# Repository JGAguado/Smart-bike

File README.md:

[![GitHub Release][releases-shield]][releases]
[![License][license-shield]](LICENSE)

[![Project Maintenance][maintenance-shield]][maintenance]
[![BuyMeCoffee][buymecoffee-shield]][buymecoffee]

# μBike
RP2040 microcontroller based board for standard bikes applications: lights control, GPS location with LoRa telemetry and display unit.

## Project tree
---

<li><a href="./uBike/Design/">Design</a></li>
<li><a href="./uBike/Documentation/">Documentation</a></li>

<li><a href="./README.md">README.md</a></li>

## Acknowledgments
---
 * [SparkFun Thing Plus RP2040](https://github.com/sparkfun/SparkFun_Thing_Plus-RP2040) - This board was used as inspiration for the layout design of the μBike

[releases-shield]: https://img.shields.io/github/release/JGAguado/uBike.svg?style=for-the-badge
[releases]: https://github.com/JGAguado/Fuel_Tracker/releases

[license-shield]: https://img.shields.io/badge/License-CC%20BY--NC--SA%204.0-lightgrey.svg?style=for-the-badge

[maintenance-shield]: https://img.shields.io/badge/maintainer-J.%20G.%20Aguado-blue.svg?style=for-the-badge
[maintenance]: https://github.com/JGAguado

[buymecoffee-shield]: https://img.shields.io/badge/buy%20me%20a%20coffee-support-yellow.svg?style=for-the-badge
[buymecoffee]: https://www.buymeacoffee.com/J.G.Aguado

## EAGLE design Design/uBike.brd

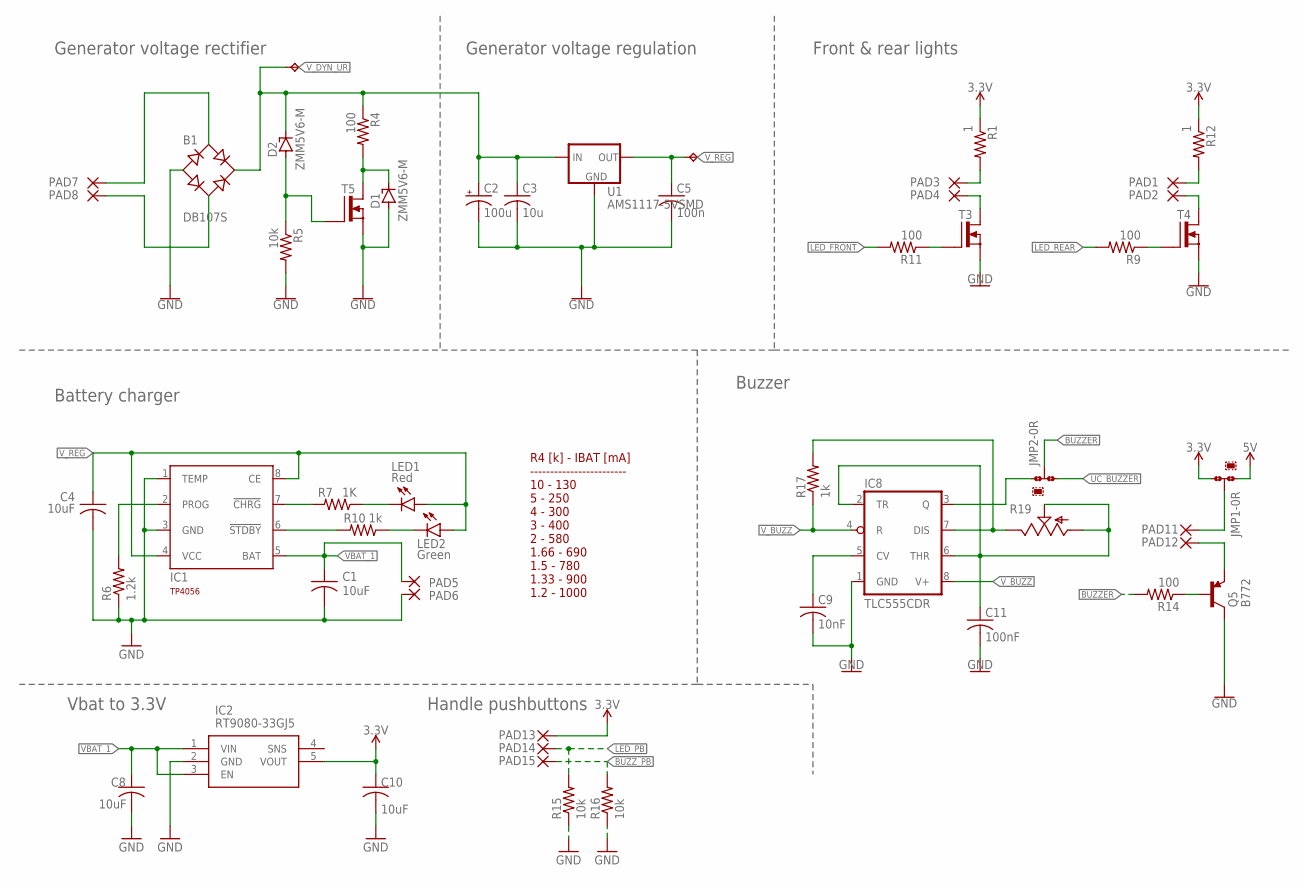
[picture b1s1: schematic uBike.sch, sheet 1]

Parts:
B1: DB107S; DBS; LCSC C5377
C1, C4, C8, C10: 10uF; C0603
C2: 100u; B/3528-21R; LCSC C16133
C3: 10u; C0603
C5: 100n; C0603
C9: 10nF; C0603
C11: 100nF; C0603
D1, D2: ZMM5V6-M; MELF-MLL34
IC1: TP4056; SOT23-8; LCSC C16581
IC2: RT9080-33GJ5; SOT94P280X100-5N; LCSC C841192
IC8: TLC555CDR; SO08; LCSC C6986
JMP1, JMP2: 0R-JUMPA; A0R-JMP
LED1: Red; LED_0603
LED2: Green; LED_0603
PAD1, PAD2, PAD3, PAD4, PAD5, PAD6, PAD7, PAD8, PAD11, PAD12, PAD13, PAD14, PAD15: SMD2; SMD1,27-2,54
Q5: B772; SOT89; LCSC C24278
R1, R12: 1; R1206; LCSC C17928
R4: 100; 0402; LCSC C17928
R5: 10k; 0402; LCSC C17928
R6: 1.2k; 0402
R7: 1K; 0402
R9, R11, R14: 100; 0402
R10, R17: 1k; 0402
R15, R16: 10k; 0402
R19: TRIM_US-RJ9W; RJ9W
T3, T4, T5: T_N-MOSFET_2N7002_CHANGJ_SOT23-GSD; SOT23
TP1, TP3: TPTP15R; TP15R
U1: AMS1117-5VSMD; SOT223

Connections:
3.3V: C10.1, IC2.5 (VOUT), JMP1.3, PAD13.1, R1.1, R12.1; also elsewhere on the board
5V: JMP1.1
BUZZER: JMP2.2, R14.2
BUZZ_PB: PAD15.1, R16.2; also elsewhere on the board
GND: B1.-, C1.2, C2.-, C3.2, C4.2, C5.2, C8.2, C9.2, C10.2, C11.2, D1.A, IC1.1 (TEMP), IC1.3 (GND), IC2.2 (GND), IC8.1 (GND), PAD6.1, Q5.2 (C), R5.2, R6.1, R15.1, R16.1, T3.2 (S), T4.2 (S), T5.2 (S), U1.1 (GND); also elsewhere on the board
LED_FRONT: R11.2; also elsewhere on the board
LED_PB: PAD14.1, R15.2; also elsewhere on the board
LED_REAR: R9.2; also elsewhere on the board
unnamed: PAD3.1, R1.2
unnamed: R9.1, T4.1 (G)
unnamed: IC1.6 (!STDBY), R10.2
unnamed: PAD4.1, T3.3 (D)
unnamed: R11.1, T3.1 (G)
unnamed: PAD2.1, T4.3 (D)
unnamed: D2.A, R5.1, T5.1 (G)
unnamed: D1.C, R4.2, T5.3 (D)
unnamed: B1.AC2, PAD8.1
unnamed: LED1.C, R7.1
unnamed: LED2.C, R10.1
unnamed: IC1.2 (PROG), R6.2
unnamed: B1.AC1, PAD7.1
unnamed: IC1.7 (!CHRG), R7.2
unnamed: Q5.1 (B), R14.1
unnamed: PAD12.1, Q5.3 (E)
unnamed: JMP1.2, PAD11.1
unnamed: PAD1.1, R12.2
unnamed: IC8.7 (DIS), R17.2, R19.E
unnamed: C11.1, IC8.2 (TR), IC8.6 (THR), R19.A, R19.S
unnamed: IC8.3 (Q), JMP2.1
unnamed: C9.1, IC8.5 (CV)
UC_BUZZER: JMP2.3; also elsewhere on the board
VBAT_1: C1.1, C8.1, IC1.5 (BAT), IC2.1 (VIN), IC2.3 (EN), PAD5.1
V_BUZZ: IC8.4 (R), IC8.8 (V+), R17.1
V_DYN_UR: B1.+, C2.+, C3.1, D2.C, R4.1, TP1.TP, U1.3 (IN)
V_REG: C4.1, C5.1, IC1.4 (VCC), IC1.8 (CE), LED1.A, LED2.A, TP3.TP, U1.2 (OUT)

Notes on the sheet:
Battery charger
R4 [k] - IBAT [mA] ------------------------ 10 - 130 5 - 250 4 - 300 3 - 400 2 - 580 1.66 - 690 1.5 - 780 1.33 - 900 1.2 - 1000
Generator voltage rectifier
Generator voltage regulation
Vbat to 3.3V
Front & rear lights
Buzzer
Handle pushbuttons

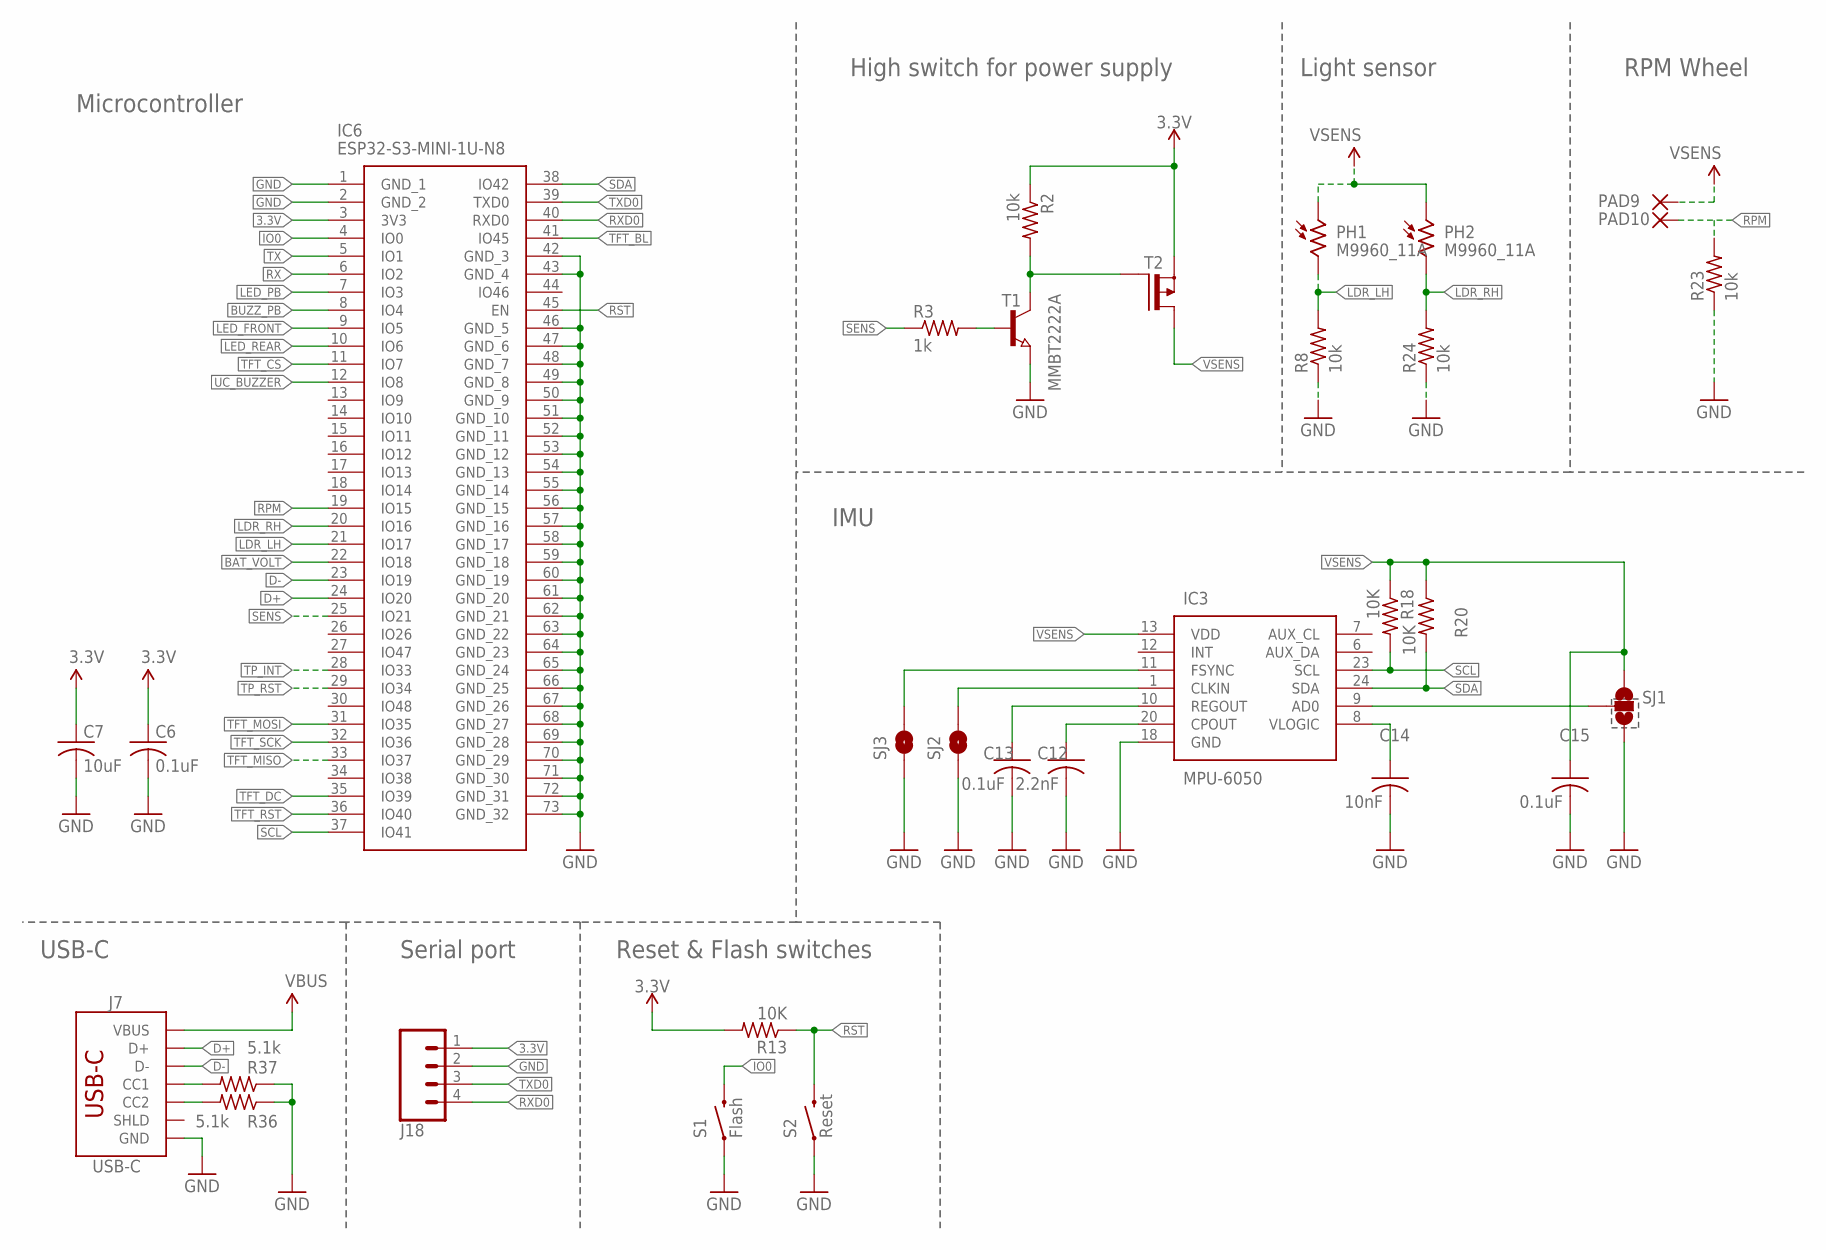
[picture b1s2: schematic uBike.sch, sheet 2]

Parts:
C6, C13, C15: 0.1uF; C0603
C7: 10uF; C0603
C12: 2.2nF; C0603
C14: 10nF; C0603
IC3: MPU-6050; MPU6050
IC6: ESP32-S3-MINI-1U-N8; ESP32S3MINI1UN8
J7: USB-C; USB-C-16P-4LAYER-ISOLATED; LCSC C2765186
J18: CONN_04PTH; 1X04
PAD9, PAD10: SMD2; SMD1,27-2,54
PH1, PH2: M9960_11A; M9960
R2, R8, R23, R24: 10k; 0402
R3: 1k; 0402
R13, R18, R20: 10K; 0402
R36, R37: 5.1k; R0603
S1: Flash; TACTILE_SWITCH_SMD_5.2MM
S2: Reset; TACTILE_SWITCH_SMD_5.2MM
SJ1: SOLDERJUMPER_2WAYPASTE2&3; SJ_3_PASTE2&3
SJ2, SJ3: SOLDERJUMPERTRACE; SJ_2S-TRACE
T1: MMBT2222A; SOT23
T2: T_P-MOSFET_SI2301CDS-T1-GE3_VISHAY_SOT23-GSD; SOT23

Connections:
3.3V: C6.1, C7.1, IC6.3 (3V3), J18.1, R2.1, R13.2, T2.2 (S); also elsewhere on the board
BAT_VOLT: IC6.22 (IO18); also elsewhere on the board
BUZZ_PB: IC6.8 (IO4); also elsewhere on the board
CC3: J7.B5 (CC2), R36.2
CC4: J7.A5 (CC1), R37.2
D+: IC6.24 (IO20), J7.A6 (D+), J7.B6 (D+)
D-: IC6.23 (IO19), J7.A7 (D-), J7.B7 (D-)
GND: C6.2, C7.2, C12.2, C13.2, C14.2, C15.2, IC3.18 (GND), IC6.1 (GND_1), IC6.2 (GND_2), IC6.42 (GND_3), IC6.43 (GND_4), IC6.46 (GND_5), IC6.47 (GND_6), IC6.48 (GND_7), IC6.49 (GND_8), IC6.50 (GND_9), IC6.51 (GND_10), IC6.52 (GND_11), IC6.53 (GND_12), IC6.54 (GND_13), IC6.55 (GND_14), IC6.56 (GND_15), IC6.57 (GND_16), IC6.58 (GND_17), IC6.59 (GND_18), IC6.60 (GND_19), IC6.61 (GND_20), IC6.62 (GND_21), IC6.63 (GND_22), IC6.64 (GND_23), IC6.65 (GND_24), IC6.66 (GND_25), IC6.67 (GND_26), IC6.68 (GND_27), IC6.69 (GND_28), IC6.70 (GND_29), IC6.71 (GND_30), IC6.72 (GND_31), IC6.73 (GND_32), J7.GND, J7.GND2 (GND), J18.2, R8.1, R23.1, R24.1, R36.1, R37.1, S1.1, S2.1, SJ1.3, SJ2.1, SJ3.1, T1.2 (E); also elsewhere on the board
IO0: IC6.4 (IO0), S1.3 (2)
LDR_LH: IC6.21 (IO17), PH1.2, R8.2
LDR_RH: IC6.20 (IO16), PH2.2, R24.2
LED_FRONT: IC6.9 (IO5); also elsewhere on the board
LED_PB: IC6.7 (IO3); also elsewhere on the board
LED_REAR: IC6.10 (IO6); also elsewhere on the board
unnamed: R2.2, T1.3 (C), T2.1 (G)
unnamed: R3.2, T1.1 (B)
unnamed: IC3.11 (FSYNC), SJ3.2
unnamed: IC3.1 (CLKIN), SJ2.2
unnamed: C13.1, IC3.10 (REGOUT)
unnamed: C12.1, IC3.20 (CPOUT)
unnamed: C14.1, IC3.8 (VLOGIC)
unnamed: IC3.9 (AD0), SJ1.2
RPM: IC6.19 (IO15), PAD10.1, R23.2
RST: IC6.45 (EN), R13.1, S2.3 (2)
RX: IC6.6 (IO2)
RXD0: IC6.40 (RXD0), J18.4
SCL: IC3.23 (SCL), IC6.37 (IO41), R18.2; also elsewhere on the board
SDA: IC3.24 (SDA), IC6.38 (IO42), R20.2; also elsewhere on the board
SENS: IC6.25 (IO21), R3.1
TFT_BL: IC6.41 (IO45); also elsewhere on the board
TFT_CS: IC6.11 (IO7); also elsewhere on the board
TFT_DC: IC6.35 (IO39); also elsewhere on the board
TFT_MISO: IC6.33 (IO37)
TFT_MOSI: IC6.31 (IO35); also elsewhere on the board
TFT_RST: IC6.36 (IO40); also elsewhere on the board
TFT_SCK: IC6.32 (IO36); also elsewhere on the board
TP_INT: IC6.28 (IO33); also elsewhere on the board
TP_RST: IC6.29 (IO34); also elsewhere on the board
TX: IC6.5 (IO1)
TXD0: IC6.39 (TXD0), J18.3
UC_BUZZER: IC6.12 (IO8); also elsewhere on the board
VBUS: J7.VBUS1 (VBUS), J7.VBUS2 (VBUS); also elsewhere on the board
VSENS: C15.1, IC3.13 (VDD), PAD9.1, PH1.1, PH2.1, R18.1, R20.1, SJ1.1, T2.3 (D); also elsewhere on the board

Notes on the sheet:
Reset & Flash switches
Serial port
Microcontroller
USB-C
High switch for power supply
Light sensor
RPM Wheel
IMU

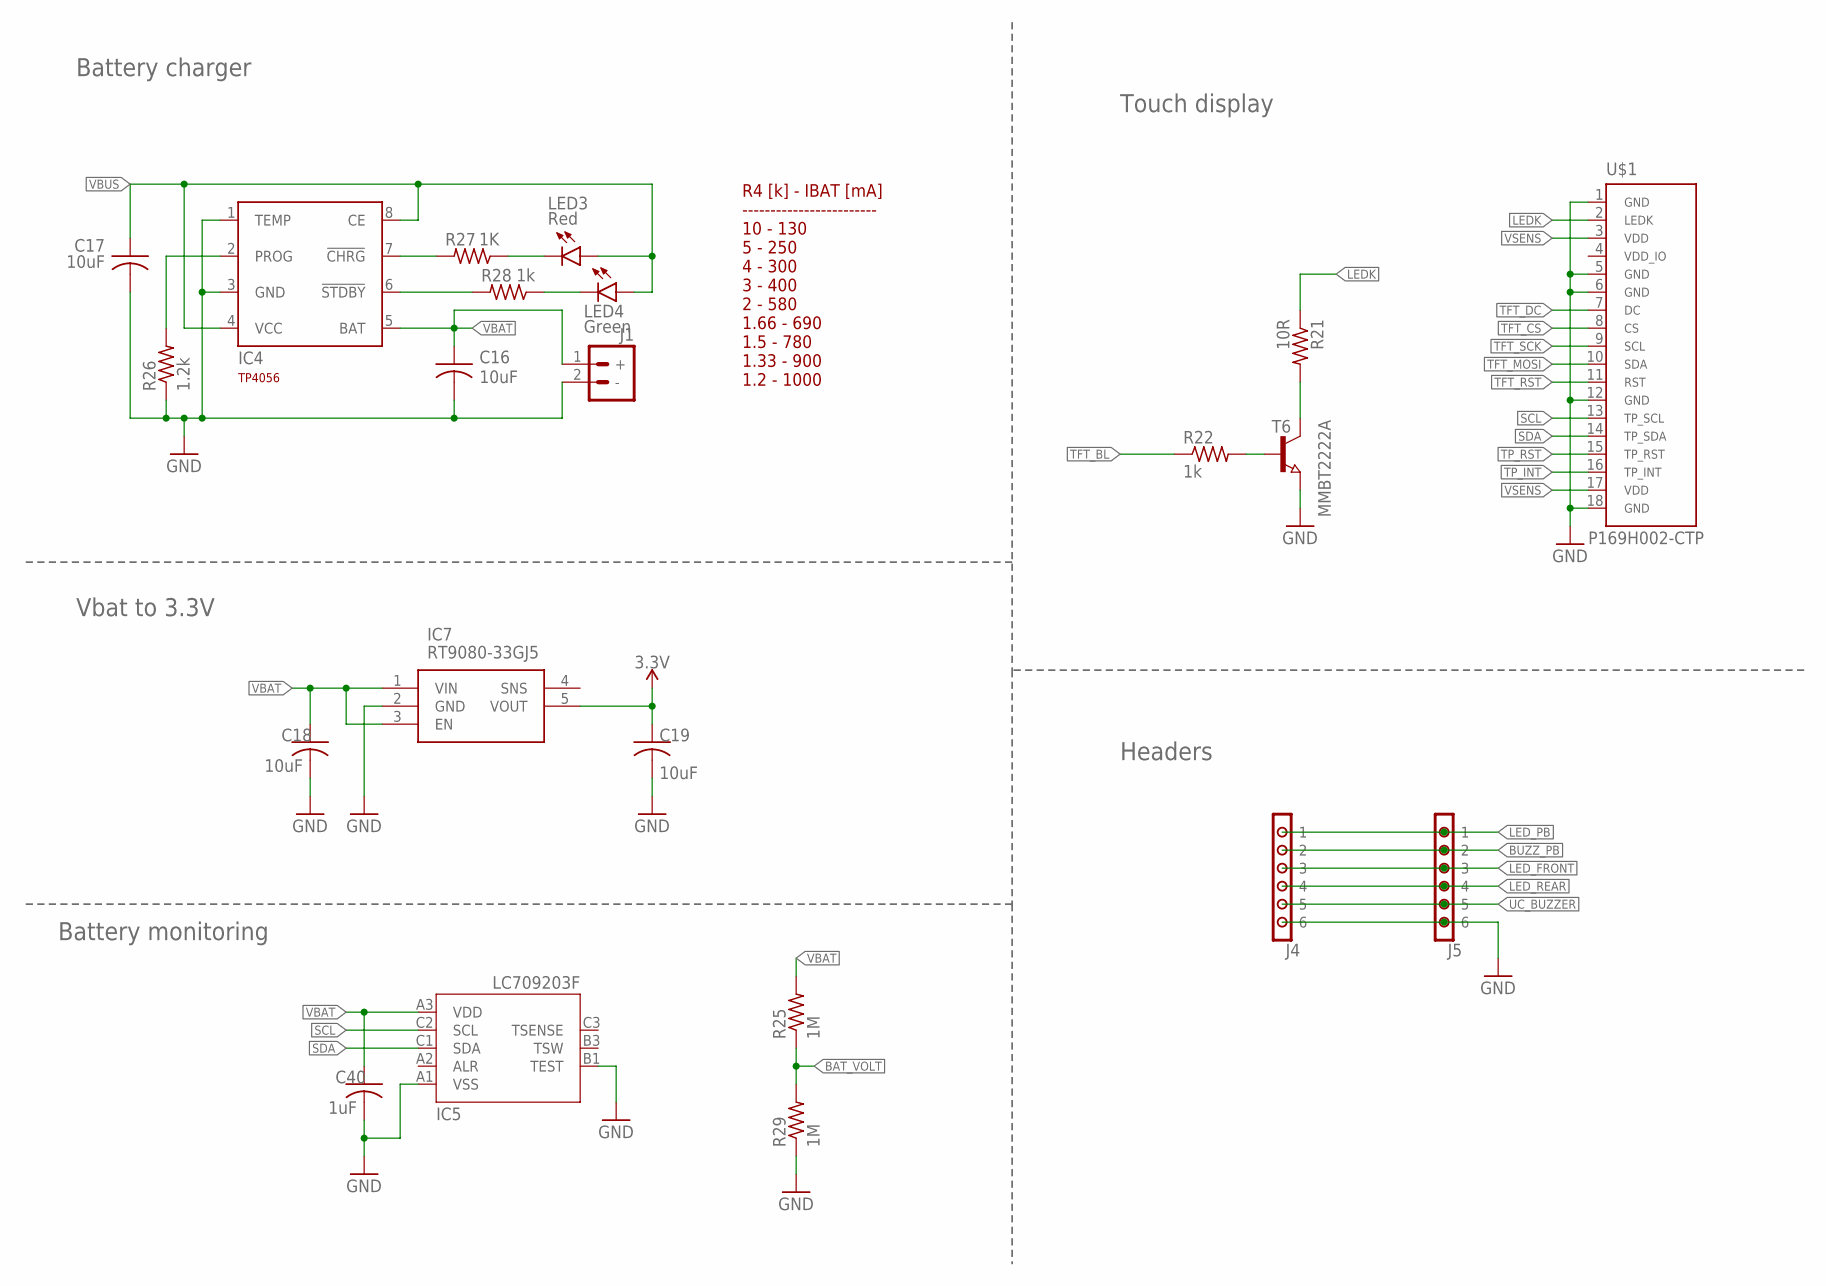
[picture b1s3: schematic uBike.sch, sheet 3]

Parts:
C16, C17, C18, C19: 10uF; C0603
C40: 1uF; C0603
IC4: TP4056; SOT23-8
IC5: LC709203F/MH; WLCSP9; LCSC C184366
IC7: RT9080-33GJ5; SOT94P280X100-5N; LCSC C841192
J1: BAT_CONN-JST-2MM-SMT; JST-2-SMD; LCSC C3029440
J4, J5: CONN_06; 1X06
LED3: Red; LED_0603
LED4: Green; LED_0603
R21: 10R; 0402
R22, R28: 1k; 0402
R25, R29: 1M; 0402
R26: 1.2k; 0402
R27: 1K; 0402
T6: MMBT2222A; SOT23
U$1: P169H002-CTP; FPC_18_0.5MM_BOTTOM; LCSC C262326

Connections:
3.3V: C19.1, IC7.5 (VOUT); also elsewhere on the board
BAT_VOLT: R25.1, R29.2; also elsewhere on the board
BUZZ_PB: J4.2, J5.2; also elsewhere on the board
GND: C16.2, C17.2, C18.2, C19.2, C40.2, IC4.1 (TEMP), IC4.3 (GND), IC5.A1 (VSS), IC5.B1 (TEST), IC7.2 (GND), J1.2 (-), J4.6, J5.6, R26.1, R29.1, T6.2 (E), U$1.1, U$1.5, U$1.6, U$1.12, U$1.18; also elsewhere on the board
LEDK: R21.1, U$1.2
LED_FRONT: J4.3, J5.3; also elsewhere on the board
LED_PB: J4.1, J5.1; also elsewhere on the board
LED_REAR: J4.4, J5.4; also elsewhere on the board
unnamed: R21.2, T6.3 (C)
unnamed: R22.2, T6.1 (B)
unnamed: IC4.6 (!STDBY), R28.2
unnamed: LED3.C, R27.1
unnamed: LED4.C, R28.1
unnamed: IC4.2 (PROG), R26.2
unnamed: IC4.7 (!CHRG), R27.2
SCL: IC5.C2 (SCL), U$1.13; also elsewhere on the board
SDA: IC5.C1 (SDA), U$1.14; also elsewhere on the board
TFT_BL: R22.1; also elsewhere on the board
TFT_CS: U$1.8; also elsewhere on the board
TFT_DC: U$1.7; also elsewhere on the board
TFT_MOSI: U$1.10; also elsewhere on the board
TFT_RST: U$1.11; also elsewhere on the board
TFT_SCK: U$1.9; also elsewhere on the board
TP_INT: U$1.16; also elsewhere on the board
TP_RST: U$1.15; also elsewhere on the board
UC_BUZZER: J4.5, J5.5; also elsewhere on the board
VBAT: C16.1, C18.1, C40.1, IC4.5 (BAT), IC5.A3 (VDD), IC7.1 (VIN), IC7.3 (EN), J1.1 (+), R25.2
VBUS: C17.1, IC4.4 (VCC), IC4.8 (CE), LED3.A, LED4.A; also elsewhere on the board
VSENS: U$1.3, U$1.17; also elsewhere on the board

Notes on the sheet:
Battery charger
R4 [k] - IBAT [mA] ------------------------ 10 - 130 5 - 250 4 - 300 3 - 400 2 - 580 1.66 - 690 1.5 - 780 1.33 - 900 1.2 - 1000
Vbat to 3.3V
Touch display
Battery monitoring
Headers

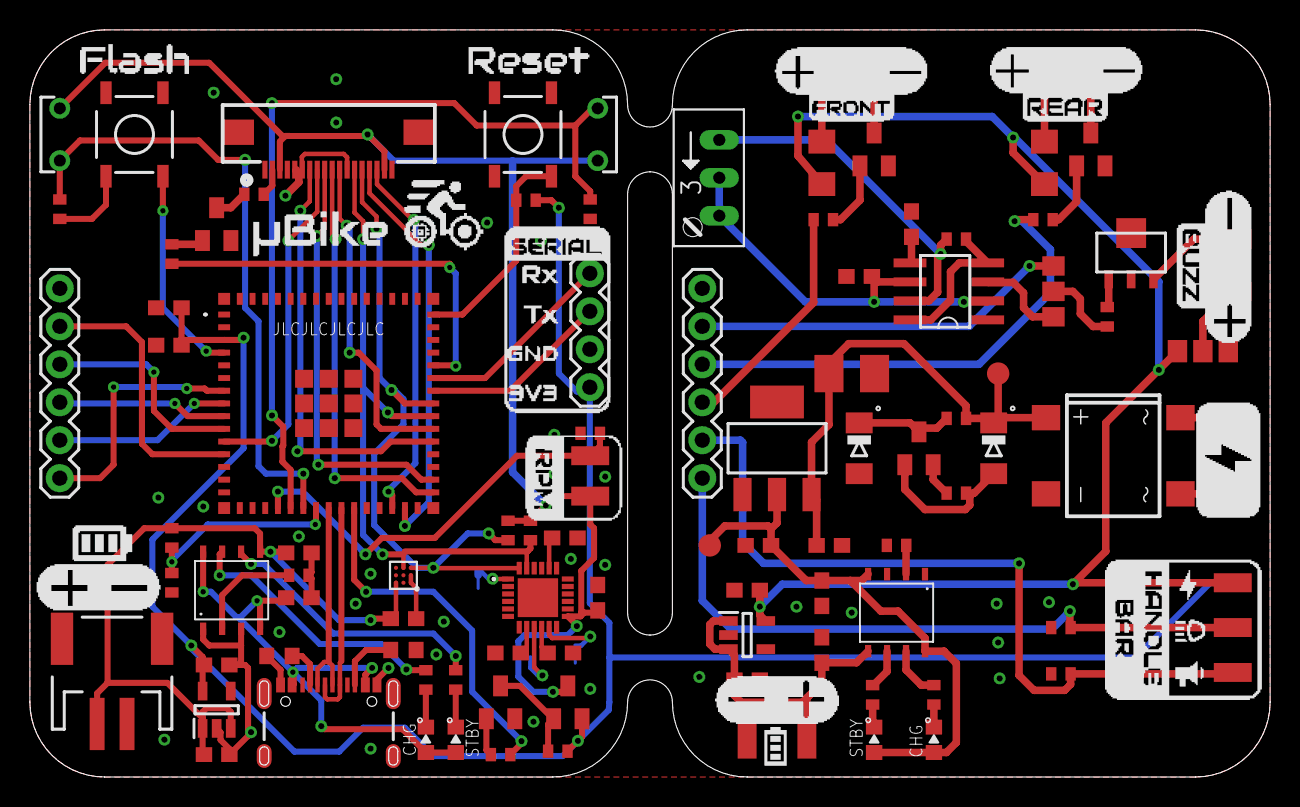
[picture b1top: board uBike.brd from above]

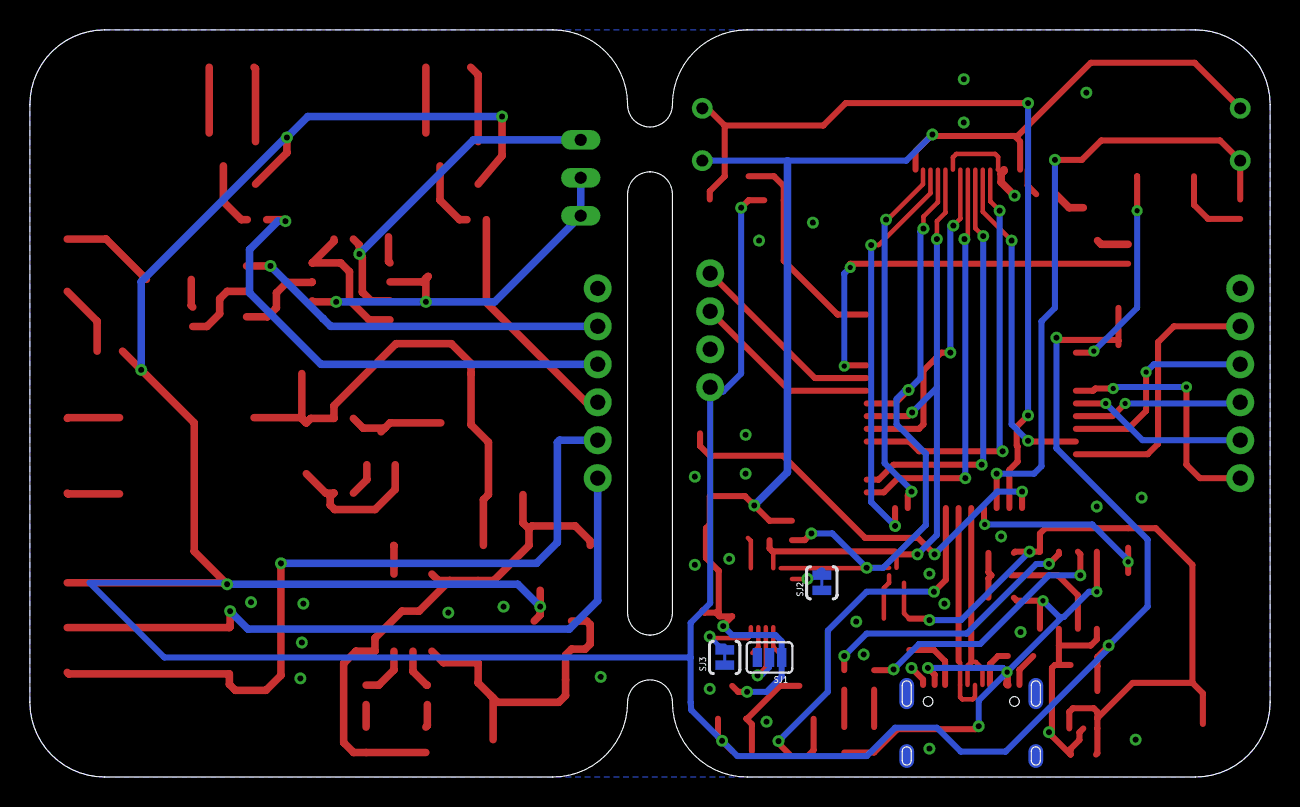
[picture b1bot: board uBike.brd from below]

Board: 2 copper layers, 83.0 x 50.0 mm, 106 parts (3 on the bottom side), 76 nets.

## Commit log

2022-03-29 First design files for uBike
2022-03-29 First documentation images and silkscreen files
2022-03-29 Updated README.md and added LICENSE
2022-03-29 Fixed documentation images path on README.md
2022-03-29 Fixed image displaying README.md
2022-03-29 New branch replacing Accel & Temp IC with pre-assembled module.
2022-03-29 Added Documentation images & Silkscreen design
2022-03-30 Added Schematics.pdf
2022-03-30 Updated silkscreen
2022-04-11 Fixed U3 component with W25Q128JVSIQ
2022-04-11 First commit in the branch
2022-04-11 Removed Bottom slk
2022-04-13 Updated schematic
2023-08-11 Frozen design for August 23 manufacturing batch
2023-08-11 Silkscreen design

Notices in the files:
parts and their libraries:
SparkFun-Connectors: Licensing: Creative Commons ShareAlike 4.0 International - https://creativecommons.org/licenses/by-sa/4.0
